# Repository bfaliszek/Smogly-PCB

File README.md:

# Smogly-PCB-ESP8266
 PCB board for [Smogly](https://github.com/hackerspace-silesia/Smogomierz) sensor

 Gerber zip file available [**HERE**](https://github.com/bfaliszek/Smogly-PCB/tree/esp8266/gerber/zip)

 Two versions available: [ESP8266](https://github.com/bfaliszek/Smogly-PCB) and [ESP32](https://github.com/bfaliszek/Smogly-PCB/tree/esp32)

## Connections with NodeMcu v3 pins

**BME280**: SDA - D3; SCL - D4

**PMSx003**: TX - D1; RX - D2

 ## Scheme

 ## 3D view

 ## Photo

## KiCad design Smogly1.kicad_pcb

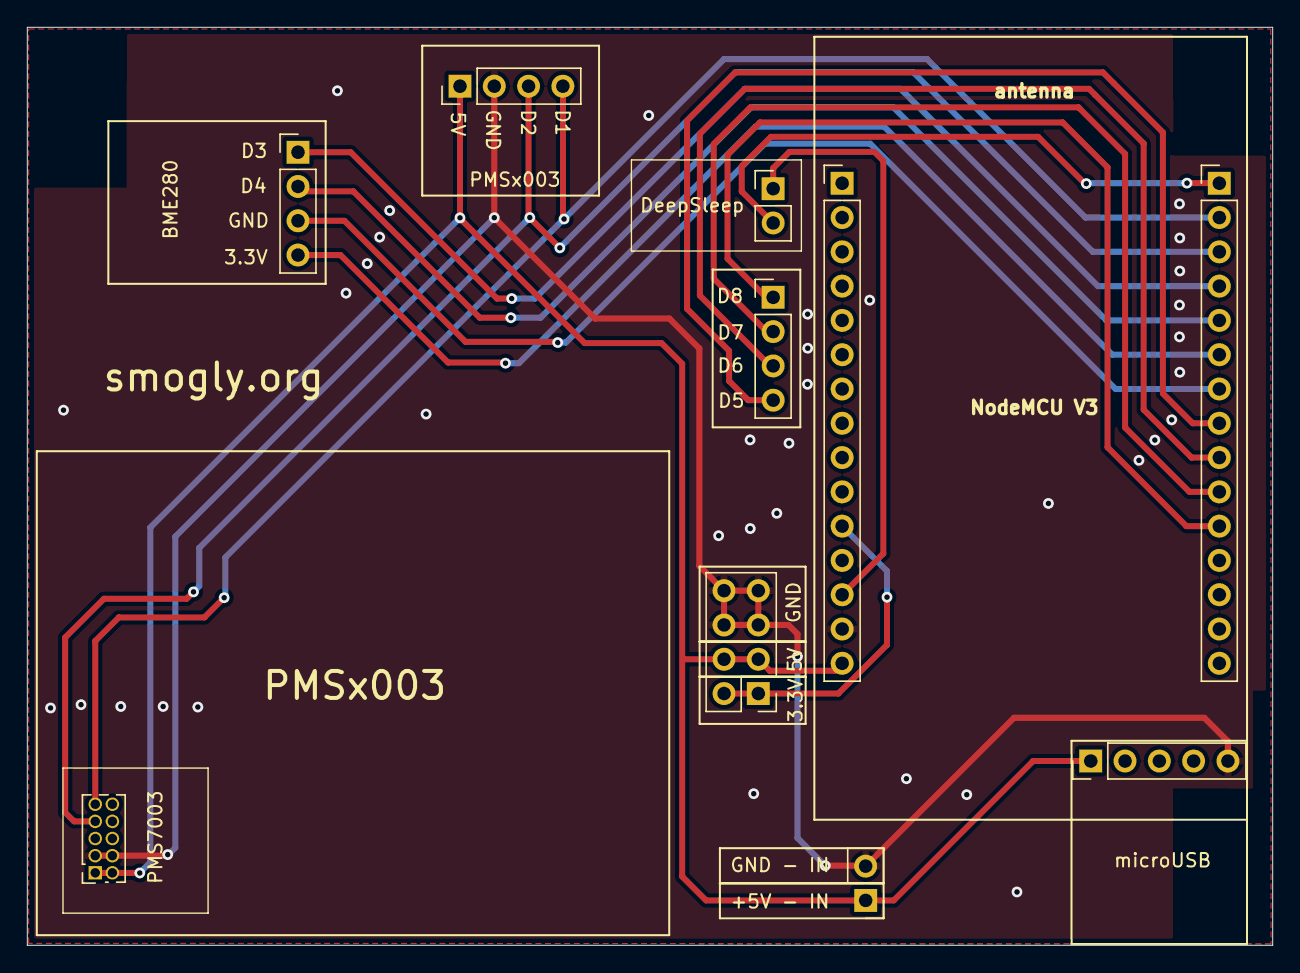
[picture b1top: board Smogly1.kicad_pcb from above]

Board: 2 copper layers, 92.2 x 68.0 mm, 10 parts (0 on the bottom side), 15 nets.

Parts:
J1: VCC IN; PinHeader_1x02_P2.54mm_Vertical
J2: PMSx003; PinHeader_1x04_P2.54mm_Vertical
J3: BME280; PinHeader_1x04_P2.54mm_Vertical
J4: microUSB; PinHeader_1x05_P2.54mm_Vertical
J5: 5/3.3/GND; PinHeader_2x04_P2.54mm_Vertical
J6: DeepSleep; PinHeader_1x02_P2.54mm_Vertical
J8: D5/6/7/8; PinHeader_1x04_P2.54mm_Vertical
J9: PMS7003_Conn; PinSocket_2x05_P1.27mm_Vertical
J10: NodeMCU A0-VIN; PinHeader_1x15_P2.54mm_Vertical
J11: NodeMCU D0-3.3V; PinHeader_1x15_P2.54mm_Vertical

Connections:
+3V3: J5.1, J5.2, J10.11
+5V: J1.1, J2.1, J4.1, J5.3, J5.4, J9.1, J9.2, J10.15
GND: J1.2, J2.2, J4.5, J5.5, J5.6, J5.7, J5.8, J9.3, J9.4, J10.14
unnamed: J6.1, J10.13
unnamed: J6.2, J11.1
unnamed: J2.4, J9.9, J11.2
unnamed: J2.3, J9.7, J11.3
unnamed: J3.1, J11.4
unnamed: J3.2, J11.5
unnamed: J3.4, J11.6
unnamed: J3.3, J11.7
unnamed: J8.4, J11.8
unnamed: J8.3, J11.9
unnamed: J8.2, J11.10
unnamed: J8.1, J11.11

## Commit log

2021-04-08 init
2021-04-20 added PMS7003 connector
2021-05-11 11.05.2021
2021-05-12 12.05.2021
2021-05-12 added photos
2022-01-05 KiCad 6.0
2022-01-05 5.01.2022
2022-01-05 ESP32 init
2022-01-05 updated files names
2022-01-26 fixed wrong BME280 power connection (switch +3/G pins)
2023-05-07 Update to KiCad 7
